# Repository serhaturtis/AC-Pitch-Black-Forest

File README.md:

<div id="top"></div>

<br />
<div align="center">

<h3 align="center">PITCH BLACK FOREST</h3>

  <p align="center">
    A Preamp Inspired By Ueberschall
  </p>
</div>

<!-- WHAT -->
## What?

This is a two stage guitar preamp board with gain, treble, mid, bass, voicing, filter bands and volume controls. And a boost switch.

## Why?

Because I wanted to experiment with JFETs and also have a small preamp board that I was going to use on another project.

## How?

This is imported from Eagle to KiCad 6 while I was backing up my projects. So the schematic's look is a bit janky.

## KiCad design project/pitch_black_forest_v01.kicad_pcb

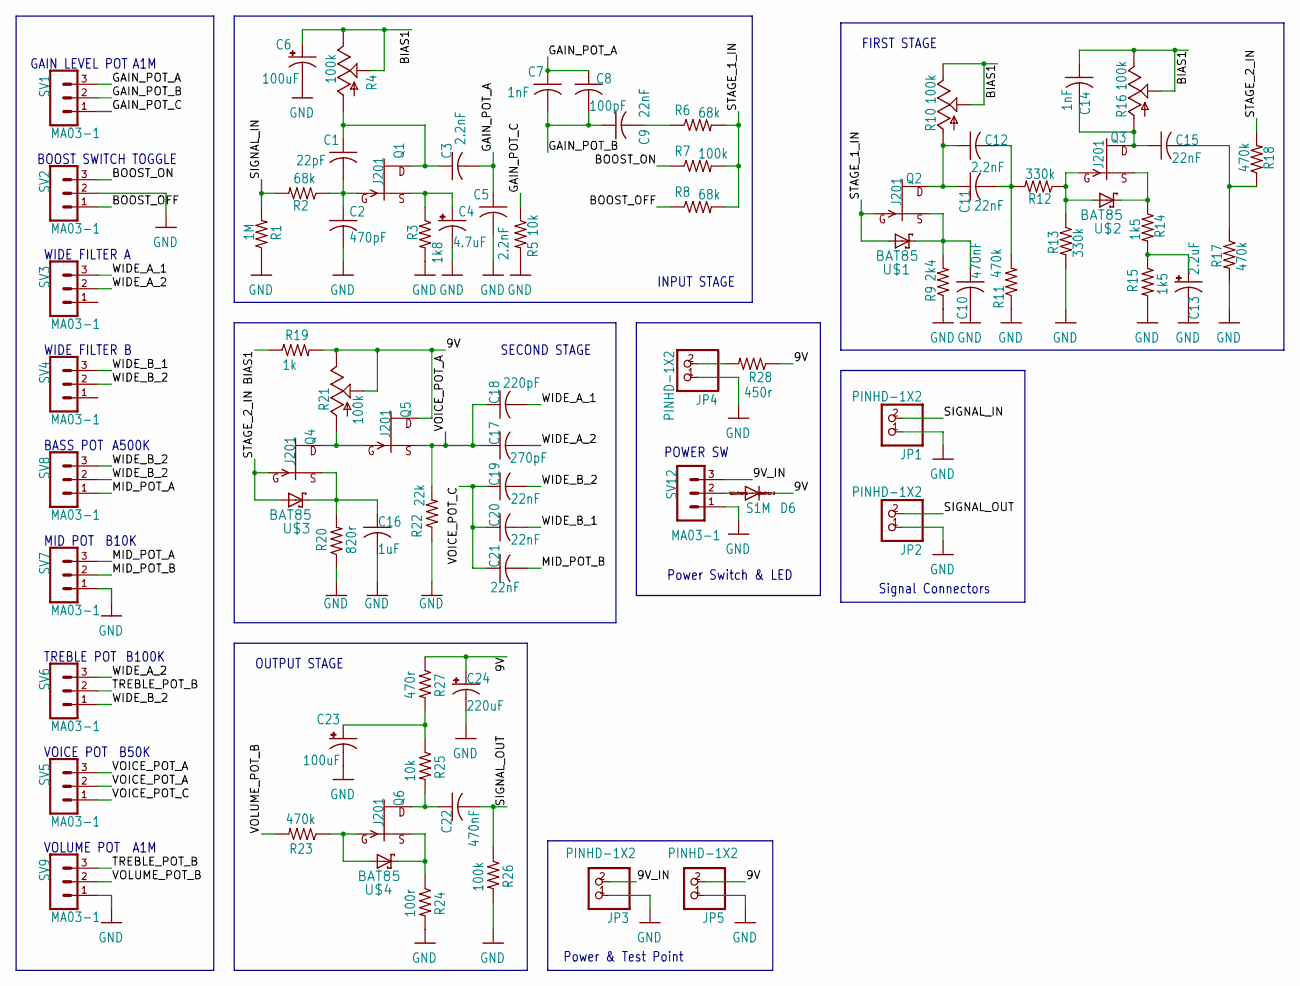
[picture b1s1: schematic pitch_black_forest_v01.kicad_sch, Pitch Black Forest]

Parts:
C1: 22pF; C0805
C2: 470pF; C0805
C3, C5, C12: 2.2nF; C0805
C4: 4.7uF; UD-4X5,8_NICHICON
C6, C23: 100uF; UD-6,3X5,8_NICHICON
C7, C14: 1nF; C0805
C8: 100pF; C0805
C9, C11, C15, C19, C20, C21: 22nF; C0805
C10, C22: 470nF; C0805
C13: 2.2uF; UD-4X5,8_NICHICON
C16: 1uF; C0805
C17: 270pF; C0805
C18: 220pF; C0805
C24: 220uF; UD-10X10_NICHICON
D6: S1M; SMA
JP1, JP2, JP3, JP4, JP5: PINHD-1X2; 1X02
Q1, Q2, Q3, Q4, Q5, Q6: J201; TO92
R1: 1M; R0805
R2, R6, R8: 68k; R0805
R3: 1k8; R0805
R4, R10, R16, R21: 100k; RJ9W
R5, R25: 10k; R0805
R7, R26: 100k; R0805
R9: 2k4; R0805
R11, R17, R18, R23: 470k; R0805
R12, R13: 330k; R0805
R14, R15: 1k5; R0805
R19: 1k; R0805
R20: 820r; R0805
R22: 22k; R0805
R24: 100r; R0805
R27: 470r; R0805
R28: 450r; R0805
SV1, SV2, SV3, SV4, SV5, SV6, SV7, SV8, SV9, SV12: MA03-1
U$1, U$2, U$3, U$4: BAT85; SOD68

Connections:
9V: C24.+, D6.C, JP5.2, Q5.3 (D), R19.2, R21.E, R21.S, R27.1, R28.1
9V_IN: JP3.2, SV12.3
BIAS1: C6.+, C14.1, R4.E, R4.S, R10.E, R10.S, R16.E, R16.S, R19.1
BOOST_OFF: R8.1, SV2.1
BOOST_ON: R7.1, SV2.3
GAIN_POT_A: C3.2, C5.1, C7.1, C8.1, SV1.3
GAIN_POT_B: C7.2, C8.2, C9.1, SV1.2
GAIN_POT_C: R5.1, SV1.1
GND: C2.2, C4.-, C5.2, C6.-, C10.2, C13.-, C16.2, C23.-, C24.-, JP1.1, JP2.1, JP3.1, JP4.1, JP5.1, R1.1, R3.2, R5.2, R9.1, R11.1, R13.2, R15.2, R17.2, R20.1, R22.1, R24.2, R26.2, SV2.2, SV7.1, SV9.1, SV12.1
MID_POT_A: SV7.3, SV8.1
MID_POT_B: C21.2, SV7.2
unnamed: C11.2, C12.2, R11.2, R12.2
unnamed: C1.2, C2.1, Q1.1 (G), R2.1
unnamed: C4.+, Q1.2 (S), R3.1
unnamed: C1.1, C3.1, Q1.3 (D), R4.A
unnamed: C9.2, R6.1
unnamed: Q3.1 (G), R12.1, R13.1, U$2.A
unnamed: C10.1, Q2.2 (S), R9.2, U$1.C (K)
unnamed: C11.1, C12.1, Q2.3 (D), R10.A
unnamed: Q3.2 (S), R14.1, U$2.C (K)
unnamed: C13.+, R14.2, R15.1
unnamed: C14.2, C15.1, Q3.3 (D), R16.A
unnamed: C15.2, R17.1, R18.1
unnamed: Q6.1 (G), R23.1, U$4.A
unnamed: C16.1, Q4.2 (S), R20.2, U$3.C (K)
unnamed: Q6.2 (S), R24.1, U$4.C (K)
unnamed: Q4.3 (D), Q5.1 (G), R21.A
unnamed: C22.1, Q6.3 (D), R25.2
unnamed: C23.+, R25.1, R27.2
unnamed: JP4.2, R28.2
unnamed: D6.A, SV12.2
SIGNAL_IN: JP1.2, R1.2, R2.2
SIGNAL_OUT: C22.2, JP2.2, R26.1
STAGE_1_IN: Q2.1 (G), R6.2, R7.2, R8.2, U$1.A
STAGE_2_IN: Q4.1 (G), R18.2, U$3.A
TREBLE_POT_B: SV6.2, SV9.3
VOICE_POT_A: C17.1, C18.1, Q5.2 (S), R22.2, SV5.2, SV5.3
VOICE_POT_C: C19.1, C20.1, C21.1, SV5.1
VOLUME_POT_B: R23.2, SV9.2
WIDE_A_1: C18.2, SV3.3
WIDE_A_2: C17.2, SV3.2, SV6.3
WIDE_B_1: C20.2, SV4.3
WIDE_B_2: C19.2, SV4.2, SV6.1, SV8.2, SV8.3

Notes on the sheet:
Signal Connectors
TREBLE POT
FIRST STAGE
B50K
BASS POT
WIDE FILTER A
VOLUME POT
A1M
VOICE POT
GAIN LEVEL POT
SECOND STAGE
B100K
A500K
MID POT
Power & Test Point
OUTPUT STAGE
Power Switch & LED
POWER SW
BOOST SWITCH TOGGLE
INPUT STAGE
WIDE FILTER B
B10K

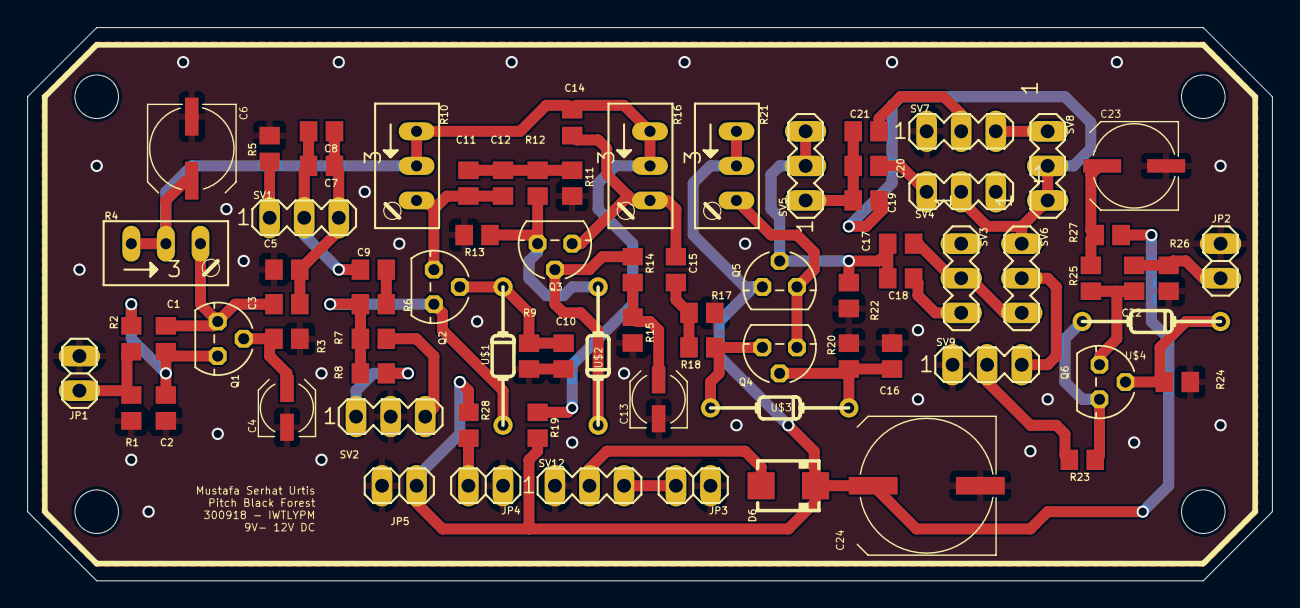
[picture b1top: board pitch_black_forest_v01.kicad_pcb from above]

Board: 2 copper layers, 91.4 x 40.6 mm, 82 parts (0 on the bottom side), 43 nets.

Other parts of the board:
@HOLE0, @HOLE1, @HOLE2, @HOLE3: (no value)

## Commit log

2022-01-11 Initial commit.
